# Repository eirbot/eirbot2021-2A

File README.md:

# EIRBOT 2021-2A : Equipe EIRBOT

Ceci est le dépôt de l'équipe de 2A de l'association de robotique Eirbot. 

## Membres
Ce projet est réalisé par les différents membres de Eirbot en première année : 
- Alberty Maxime (SEE)
- Barrais Marius
- Camberlin Erwann (Matmeca)
- Delpeuch Sébastien (Informatique)
- Mangin Lucas
- Moroy Liam
- Neveu Emile
- Pouget Filipe
- Poupon Julien
- Savary Clément (SEE)
- Vaquori Yohann
- Vidal Martin

## Organisation du projet 

Le projet est découpé selon 4 axes correspondant aux 4 domaines de la construction de notre robot. La conception mécanique du robot est disponible dans le dossier `meca/`, les fichiers ont été réalisés sur Solidworks / onshape. La réalisation du robot a été faite grâce à des imprimantes 3D, découpeuse laser et fraiseuse disponibles au fablab de l'école. Dans le dossier `elec/` les différents fichiers des cartes électroniques que nous avons réalisé sont disponibles (fichiers kicad), elles ont été réalisées grâce à la chimie de l'enseirb et à la fraiseuse du fablab. Le dossier `spec/`contient tous les fichiers d'organisation de l'équipe. Finalement le dossier `code/`contient les différents code de ntore robot, un tutoriel dpour les déployer est disponible ci dessous.

## 🦠 Covid-19

Suite à la pandémie de covid-19 la coupe de France de robotique a été déplacé à juillet 2021. Malheureusement, l'association étant composée d'élèves ingénieurs ces derniers sont en stage sur cette période nous n'avons pas pu participer à cette édition. 

Eirbot a cependant été représenté par des anciens de l'association, l'équipe [Pokibot](https://github.com/Pokibot-org/pokirobotsoft)

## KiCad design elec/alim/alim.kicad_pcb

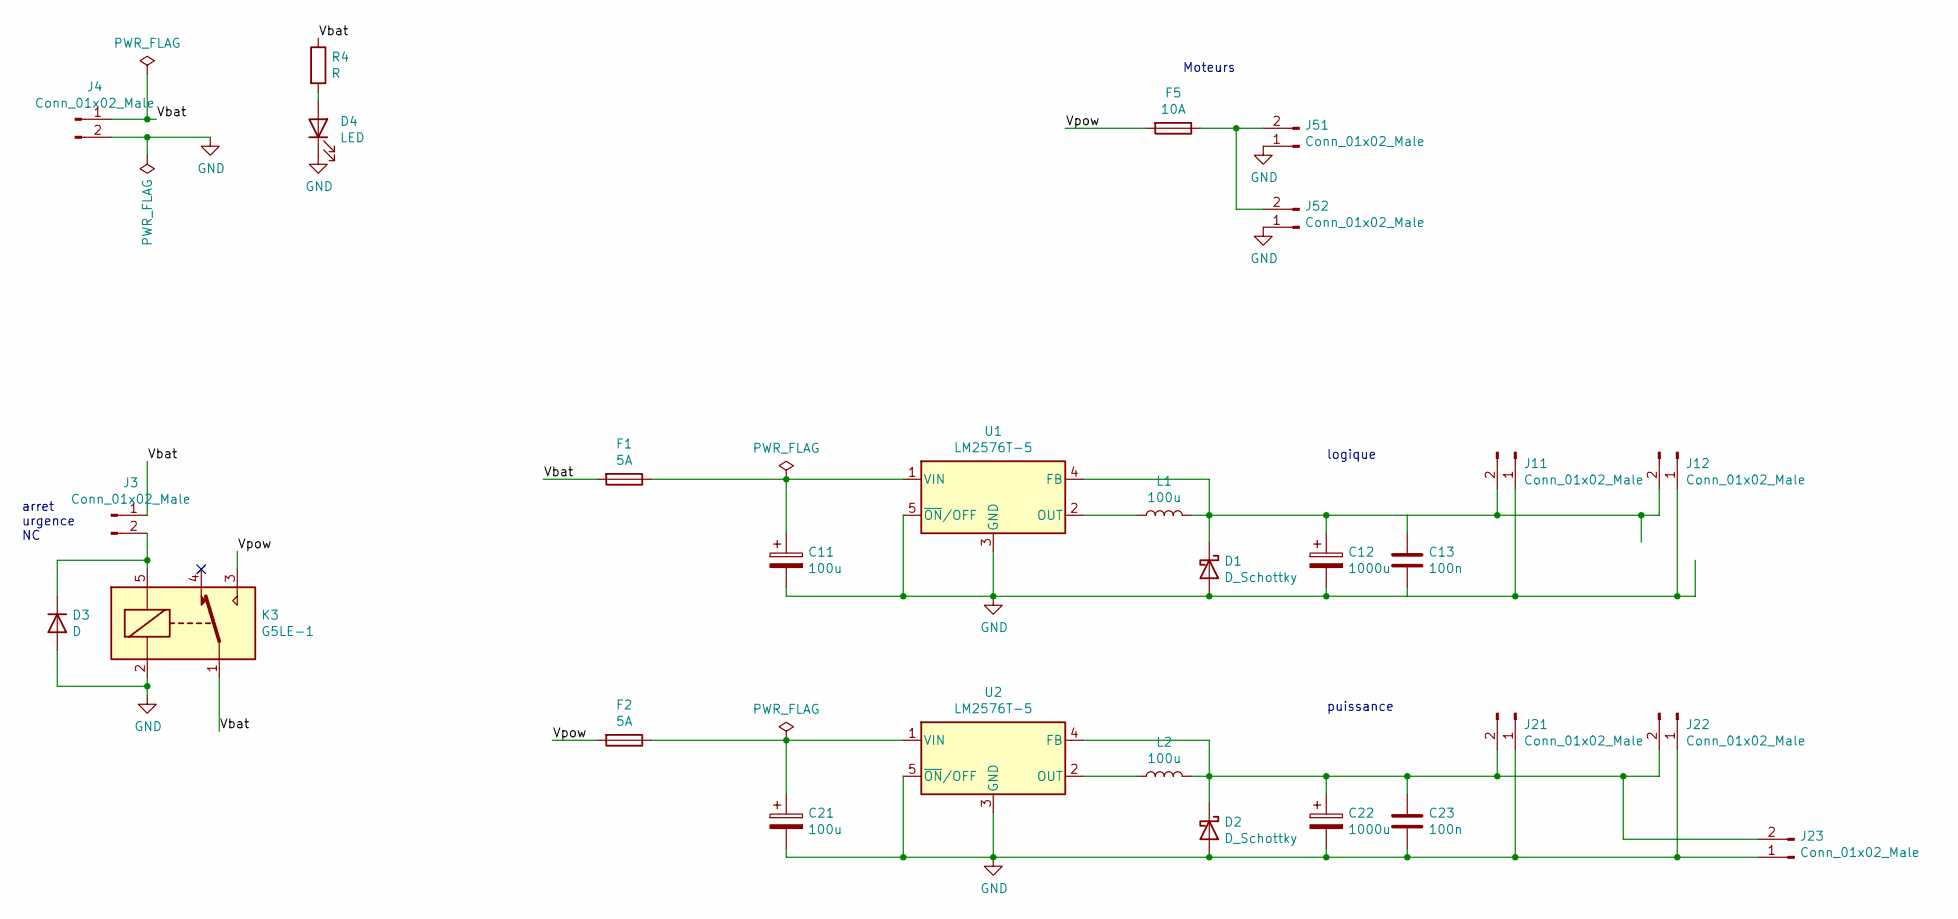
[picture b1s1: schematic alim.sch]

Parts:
C11, C21: 100u; CP_Radial_D10.0mm_P5.00mm
C12, C22: 1000u; CP_Radial_D10.0mm_P5.00mm
C13, C23: 100n; C_1206_3216Metric_Pad1.33x1.80mm_HandSolder
D1, D2: D_Schottky; D_DO-27_P12.70mm_Horizontal
D3: D; D_DO-27_P12.70mm_Horizontal
D4: LED; LED_D3.0mm
F1, F2: 5A; fusible_alim
F5: 10A; fusible_alim
J3, J4, J11, J12, J21, J22, J51, J52: Conn_01x02_Male; TerminalBlock_bornier-2_P5.08mm
J23: Conn_01x02_Male; SolderWire-0.127sqmm_1x02_P3.7mm_D0.48mm_OD1mm
K3: G5LE-1; Relay_SPDT_Omron-G5LE-1
L1, L2: 100u; L_Toroid_Vertical_L16.5mm_W11.4mm_P7.62mm_Pulse_KM-2
R4: R; R_Axial_DIN0411_L9.9mm_D3.6mm_P5.08mm_Vertical
U1, U2: LM2576T-5; TO-220-5_P3.4x3.7mm_StaggerEven_Lead3.8mm_Vertical

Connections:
/Vbat: F1.2, J3.1, J4.1, K3.1, R4.1
/Vpow: F2.2, F5.2, K3.3
GND: C11.2, C12.2, C13.2, C21.2, C22.2, C23.2, D1.2 (A), D2.2 (A), D3.2 (A), D4.1 (K), J4.2, J11.1, J12.1, J21.1, J22.1, J23.1, J51.1, J52.1, K3.2, U1.3 (GND), U1.5 (~ON~/OFF), U2.3 (GND), U2.5 (~ON~/OFF)
unnamed: C11.1, F1.1, U1.1 (VIN)
unnamed: C12.1, C13.1, D1.1 (K), J11.2, J12.2, L1.2, U1.4 (FB)
unnamed: C21.1, F2.1, U2.1 (VIN)
unnamed: C22.1, C23.1, D2.1 (K), J21.2, J22.2, J23.2, L2.2, U2.4 (FB)
unnamed: D3.1 (K), J3.2, K3.5
unnamed: D4.2 (A), R4.2
unnamed: F5.1, J51.2, J52.2
unnamed: L1.1, U1.2 (OUT)
unnamed: L2.1, U2.2 (OUT)

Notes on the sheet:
Moteurs
arret urgence NC
logique
puissance

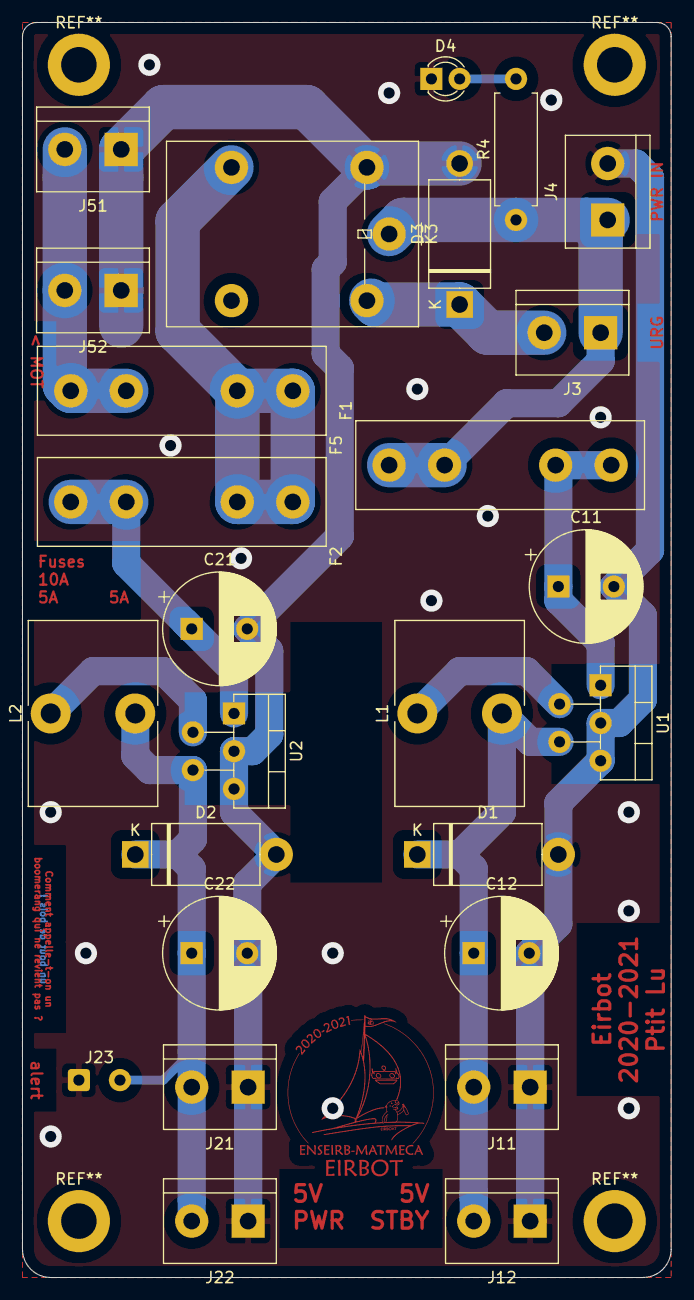
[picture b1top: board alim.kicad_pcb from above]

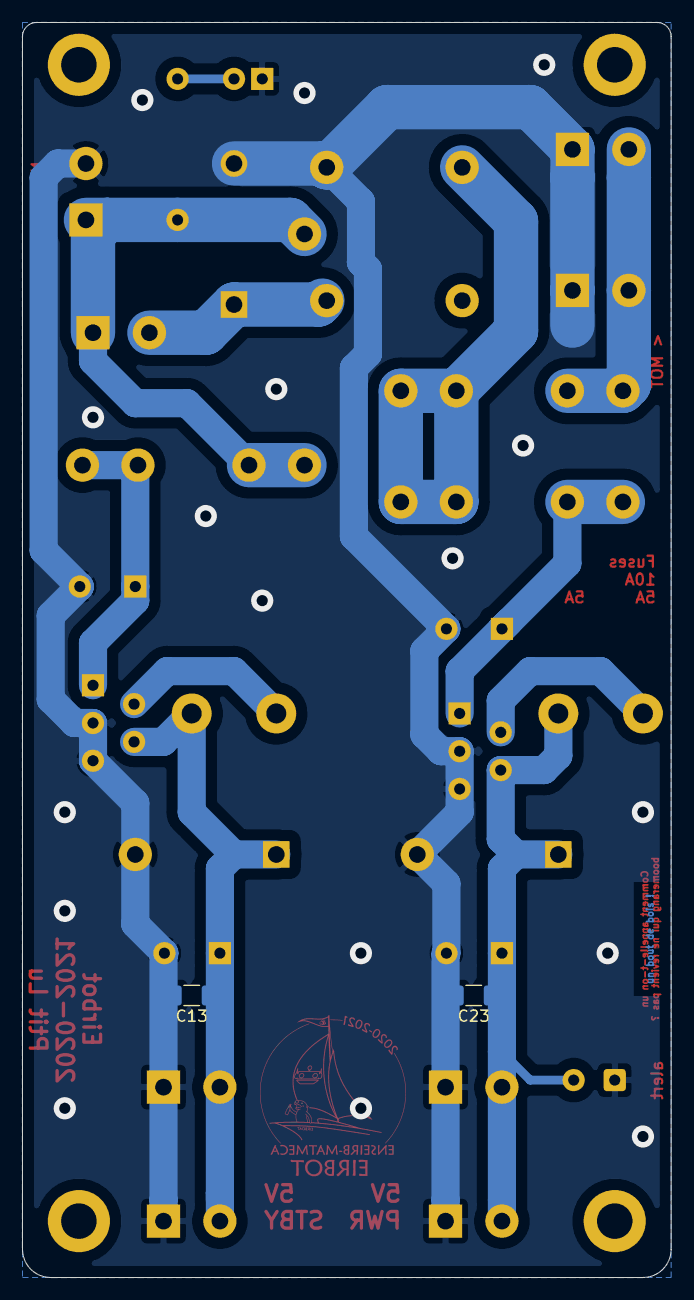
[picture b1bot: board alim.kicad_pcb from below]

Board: 2 copper layers, 58.4 x 113.0 mm, 28 parts (2 on the bottom side), 12 nets.

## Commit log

2020-11-11 INIT
2020-11-11 add .github
2021-01-31 SPEC : somes notes
2021-02-02 Ajout début Méca
2021-02-03 modifs méca
2021-02-04 encore des changemets
2021-02-05 Toujours des changements sur la méca
2021-02-08 toujours des modifs
2021-02-09 MECA : ajout des STL
2021-02-10 MECA : Ajout du trou du bouton d'arrêt d'urgence
2021-02-10 MECA : modele plaque du haut pour la laser
2021-02-11 MECA : laser cut file
2021-02-23 add alim kicad
2021-02-24 debut uniformisation des trous
2021-02-24 ajout des fichiers typons, drill, ...
2021-02-24 fin uniformisation des trous
2021-02-25 MECA : ajout equerre
2021-02-25 modif fusibles
2021-03-03 INFO : init structure
2021-03-03 CODE : first skeleton
2021-03-03 CODE : compilation tools
2021-03-05 CODE : add documentation for workflow test
2021-03-05 CODE : compilation fix
2021-03-05 CODE : add a usefull test
2021-03-05 deploy: 197cdd7edf0285821534ef4ee5854ee6549c8dcd
2021-03-07 CODE : update cmakelist.txt
2021-03-07 CODE : add documentation
2021-03-07 CODE : fix debug class
2021-03-07 SONARQUBE : deploy
2021-03-07 modif finales et impression
2021-03-09 MECA : ajouts STL
2021-03-10 CODE : add asserv folder
2021-03-10 MECA : Ajout STL
2021-03-11 structure platformio
2021-03-11 CODE : ajout asserv
2021-03-16 deploy: 62a91f7f26236bf3b2fad6eaf7d18f900d3e8183
2021-08-04 Close project
